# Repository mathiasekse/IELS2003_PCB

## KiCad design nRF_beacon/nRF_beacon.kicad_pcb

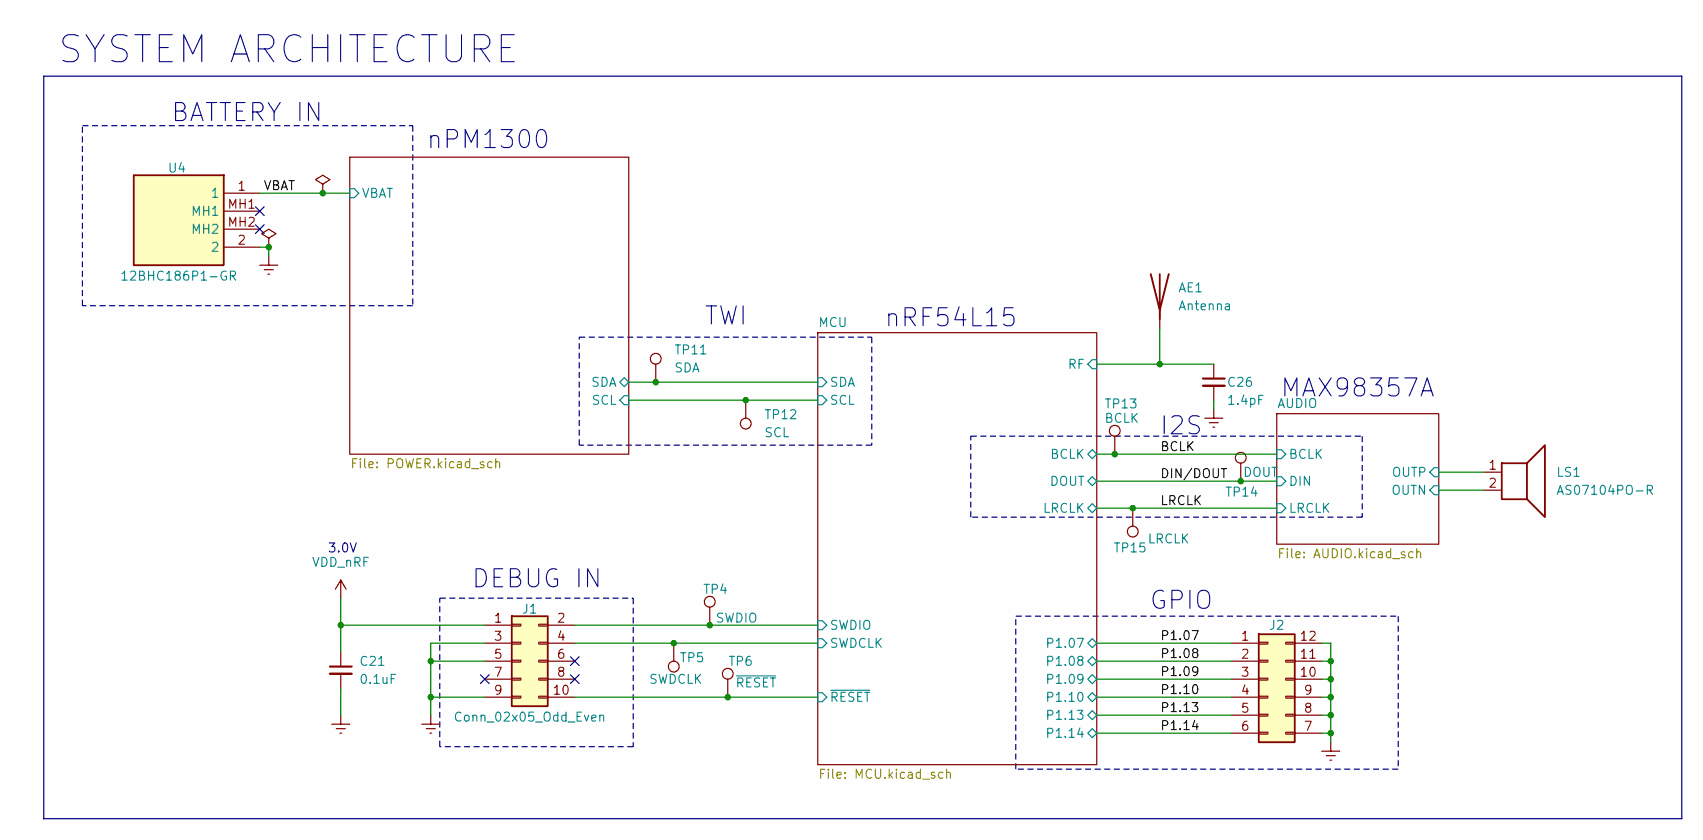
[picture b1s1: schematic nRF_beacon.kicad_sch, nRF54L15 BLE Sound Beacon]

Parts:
AE1: Antenna; PCB_Antenna
C21: 0.1uF; C_0201_0603Metric; MPN KGM03BR51E104KH
C26: 1.4pF; C_0201_0603Metric; MPN GCQ0335C1H1R4WB01D
J1: Conn_02x05_Odd_Even; FTSH-105-XX-YYY-DV-K-P-TR; MPN FTSH-105-01-F-DV-K-P
J2: Conn_02x03_Counter_Clockwise; PinHeader_2x06_P2.54mm_Vertical
LS1: AS07104PO-R; VN02A1500000G; MPN AS07104PO-R
TP4: SWDIO; TestPoint_Pad_D1.0mm
TP5: SWDCLK; TestPoint_Pad_D1.0mm
TP6: ~{RESET}; TestPoint_Pad_D1.0mm
TP11: SDA; TestPoint_Pad_D1.0mm
TP12: SCL; TestPoint_Pad_D1.0mm
TP13: BCLK; TestPoint_Pad_D1.0mm
TP14: DOUT; TestPoint_Pad_D1.0mm
TP15: LRCLK; TestPoint_Pad_D1.0mm
U4: 12BHC186P1-GR; 12BHC186P1GR; Manufacturer_Part_Number 12BHC186P1-GR; Mouser Part Number 12BHC186P1-GR

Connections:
/AUDIO/OUTN: LS1.2; also elsewhere on the board
/AUDIO/OUTP: LS1.1; also elsewhere on the board
/BCLK: TP13.1; also elsewhere on the board
/DIN/DOUT: TP14.1; also elsewhere on the board
/LRCLK: TP15.1; also elsewhere on the board
/MCU/RF: AE1.1 (A), C26.1; also elsewhere on the board
/MCU/SCL: TP12.1; also elsewhere on the board
/MCU/SDA: TP11.1; also elsewhere on the board
/MCU/SWDCLK: J1.4, TP5.1; also elsewhere on the board
/MCU/SWDIO: J1.2, TP4.1; also elsewhere on the board
/MCU/~RESET: J1.10, TP6.1; also elsewhere on the board
/P1.07: J2.1; also elsewhere on the board
/P1.08: J2.2; also elsewhere on the board
/P1.09: J2.3; also elsewhere on the board
/P1.10: J2.4; also elsewhere on the board
/P1.13: J2.5; also elsewhere on the board
/P1.14: J2.6; also elsewhere on the board
/VBAT: U4.1; also elsewhere on the board
GND: C21.2, C26.2, J1.3, J1.5, J1.9, J2.7, J2.8, J2.9, J2.10, J2.11, J2.12, U4.2; also elsewhere on the board
VDD_nRF: C21.1, J1.1; also elsewhere on the board

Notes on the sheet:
nPM1300
DEBUG IN
BATTERY IN
I2S
3.0V
GPIO
nRF54L15
TWI
SYSTEM ARCHITECTURE
MAX98357A

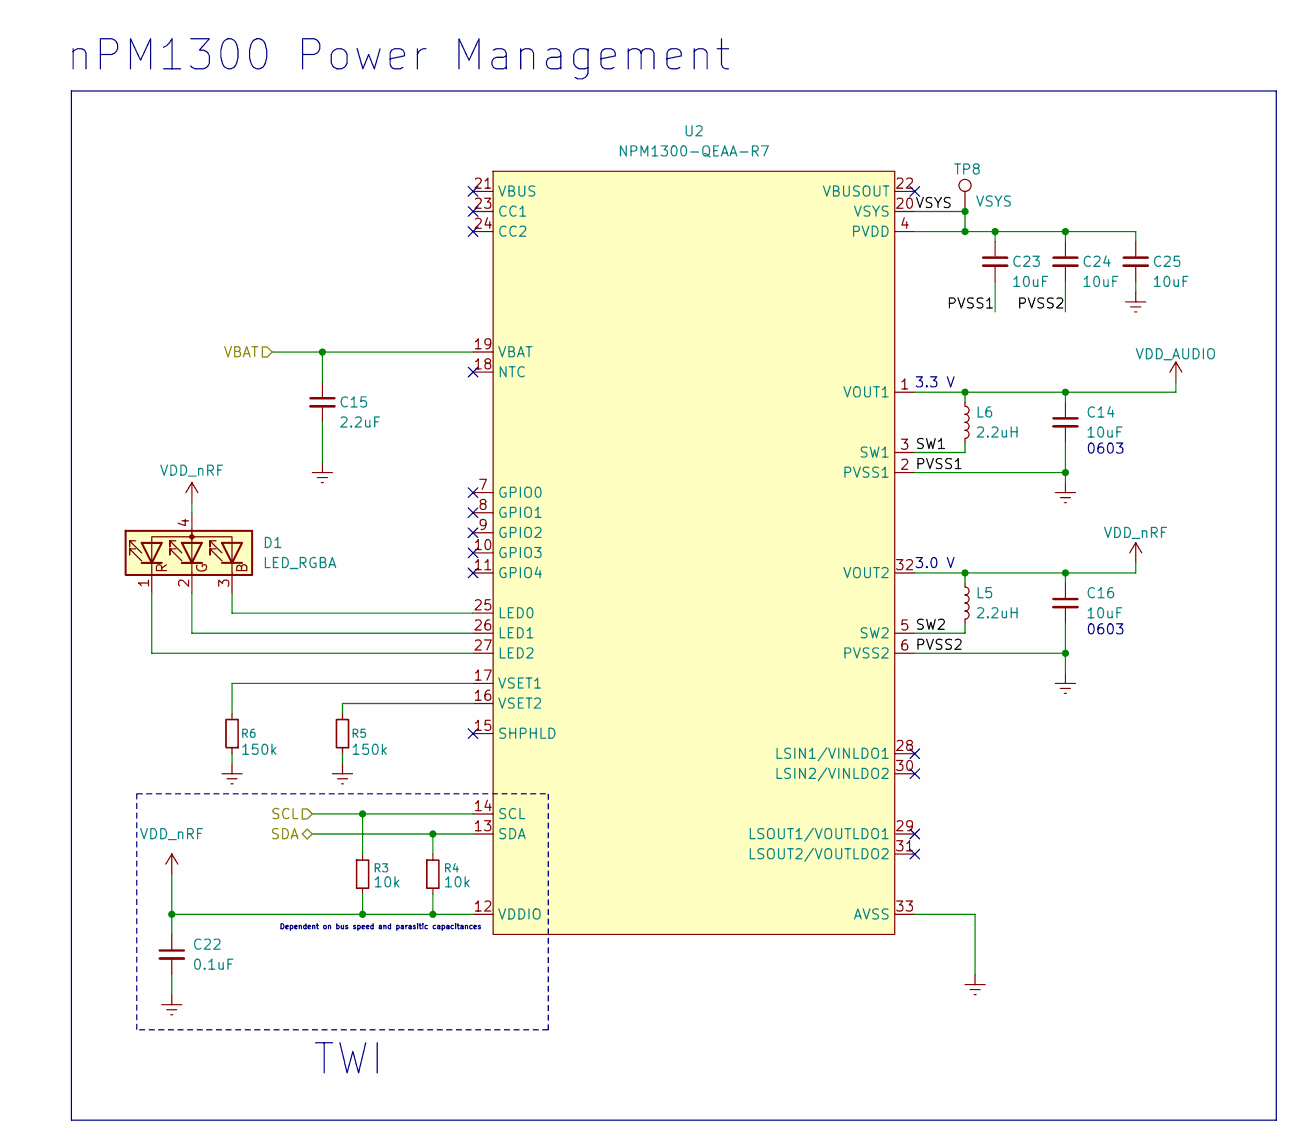
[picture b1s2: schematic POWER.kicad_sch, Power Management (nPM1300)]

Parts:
C14, C16, C23, C24, C25: 10uF; C_0603_1608Metric; MPN KGM15CR51E106KT
C15: 2.2uF; C_0603_1608Metric; MPN GRM188Z71C225KE43D
C22: 0.1uF; C_0201_0603Metric; MPN KGM03BR51E104KH
D1: LED_RGBA; APGF1012GBRC07; MPN APGF1012GBRC-07
L5, L6: 2.2uH; INDC2016X100N; MPN MLP2016V2R2MT0S1
R3, R4: 10k; R_0402_1005Metric; MPN CRCW040210K0FHEDP
R5, R6: 150k; R_0201_0603Metric; MPN CRCW0201150KFKED
TP8: VSYS; TestPoint_Pad_D1.0mm
U2: NPM1300-QEAA-R7; QFN-32_EP_5x5_Pitch0.5mm; MPN NPM1300-QEAA-R7

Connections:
/MCU/SCL: R3.1, U2.14 (SCL); also elsewhere on the board
/MCU/SDA: R4.1, U2.13 (SDA); also elsewhere on the board
/POWER/SW1: L6.2, U2.3 (SW1)
/POWER/SW2: L5.2, U2.5 (SW2)
/POWER/VSYS: C23.1, C24.1, C25.1, TP8.1, U2.4 (PVDD), U2.20 (VSYS)
/VBAT: C15.1, U2.19 (VBAT); also elsewhere on the board
GND: C14.2, C15.2, C16.2, C22.2, C23.2, C24.2, C25.2, R5.1, R6.1, U2.2 (PVSS1), U2.6 (PVSS2), U2.33 (AVSS); also elsewhere on the board
unnamed: D1.3 (BK), U2.25 (LED0)
unnamed: D1.2 (GK), U2.26 (LED1)
unnamed: D1.1 (RK), U2.27 (LED2)
unnamed: R6.2, U2.17 (VSET1)
unnamed: R5.2, U2.16 (VSET2)
VDD_AUDIO: C14.1, L6.1, U2.1 (VOUT1); also elsewhere on the board
VDD_nRF: C16.1, C22.1, D1.4 (A), L5.1, R3.2, R4.2, U2.12 (VDDIO), U2.32 (VOUT2); also elsewhere on the board

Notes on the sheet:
0603
TWI
3.3 V
nPM1300 Power Management
Dependent on bus speed and parasitic capacitances
3.0 V

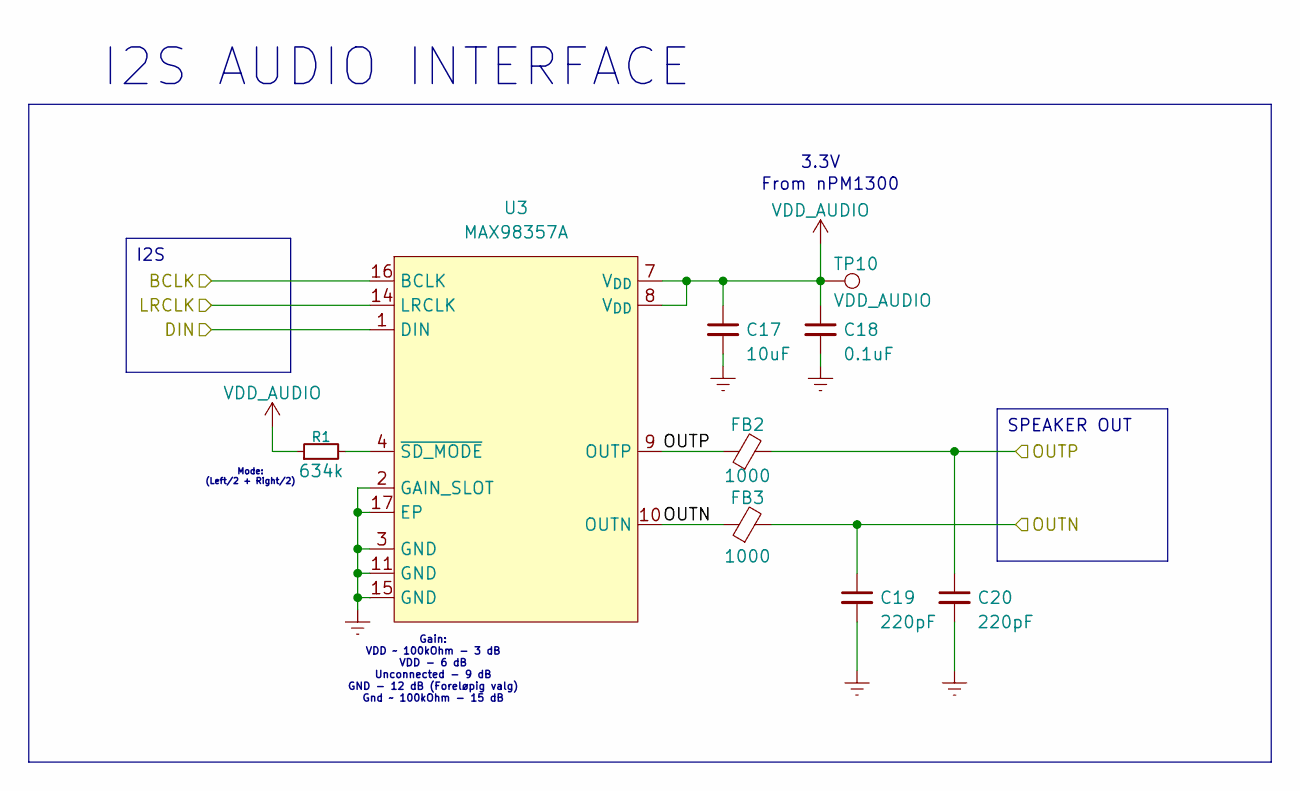
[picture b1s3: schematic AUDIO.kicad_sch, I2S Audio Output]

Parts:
C17: 10uF; C_0603_1608Metric; MPN KGM15CR51E106KT
C18: 0.1uF; C_0201_0603Metric; MPN KGM03BR51E104KH
C19, C20: 220pF; C_0603_1608Metric; MPN C0603C221J5RACTM
FB2, FB3: 1000; C_0805_2012Metric; MPN BLM21SP102SN1D
R1: 634k; R_0603_1608Metric; MPN CRCW0603634KDHTAP
TP10: VDD_AUDIO; TestPoint_Pad_D1.0mm
U3: MAX98357A; TQFN-16-1EP_3x3mm_P0.5mm_EP1.6x1.6mm; MPN MAX98357AETE+T

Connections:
/AUDIO/OUTN: C19.1, FB3.1, FB3.2, U3.10 (OUTN); also elsewhere on the board
/AUDIO/OUTP: C20.1, FB2.1, FB2.2, U3.9 (OUTP); also elsewhere on the board
/BCLK: U3.16 (BCLK); also elsewhere on the board
/DIN/DOUT: U3.1 (DIN); also elsewhere on the board
/LRCLK: U3.14 (LRCLK); also elsewhere on the board
GND: C17.2, C18.2, C19.2, C20.2, U3.2 (GAIN_SLOT), U3.3 (GND), U3.11 (GND), U3.15 (GND), U3.17 (EP); also elsewhere on the board
unnamed: R1.2, U3.4 (~SD_MODE)
VDD_AUDIO: C17.1, C18.1, R1.1, TP10.1, U3.7 (V_{DD}), U3.8 (V_{DD}); also elsewhere on the board

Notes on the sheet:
Gain: VDD ~ 100kOhm - 3 dB VDD - 6 dB Unconnected - 9 dB GND - 12 dB (Foreløpig valg) Gnd ~ 100kOhm - 15 dB
Mode: (Left/2 + Right/2)
From nPM1300
I2S AUDIO INTERFACE
3.3V
SPEAKER OUT
I2S

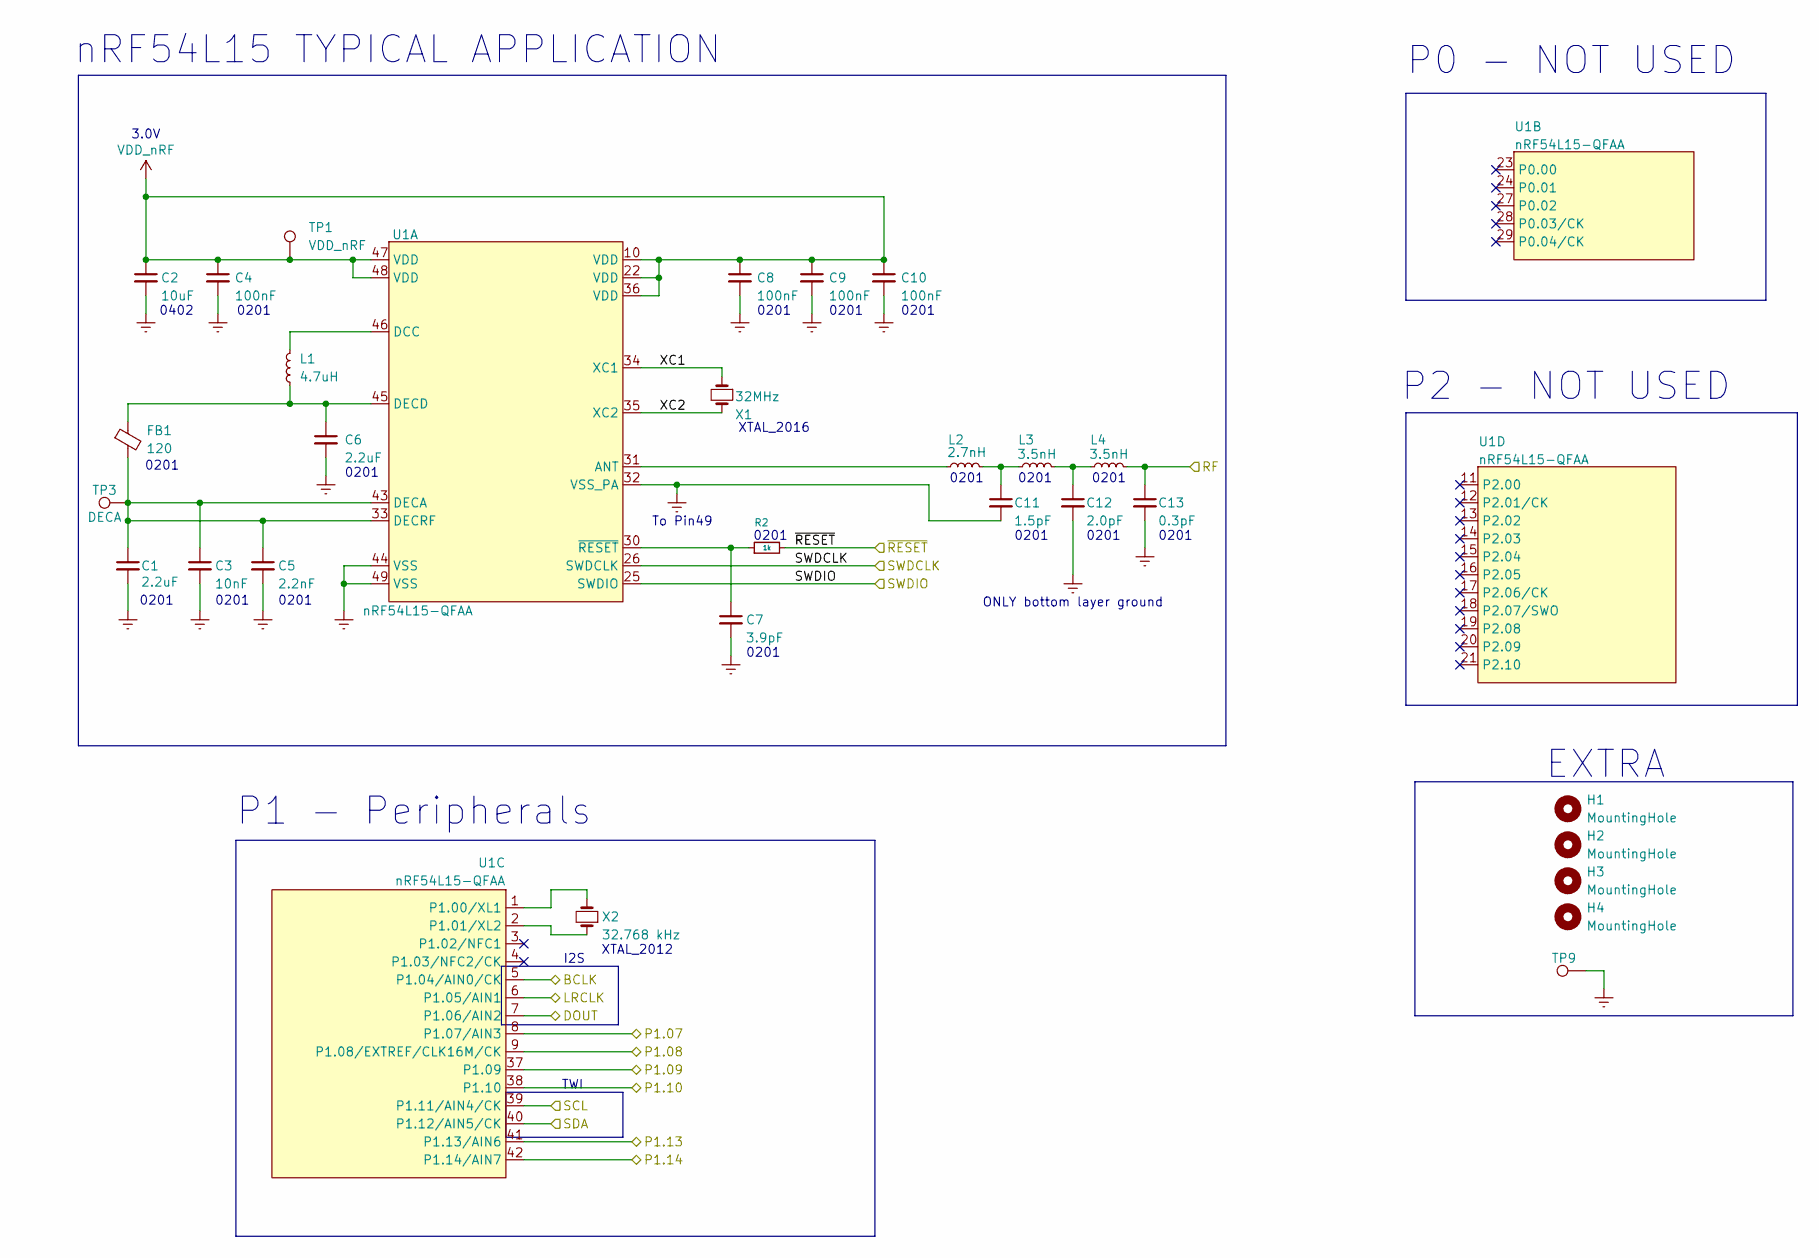
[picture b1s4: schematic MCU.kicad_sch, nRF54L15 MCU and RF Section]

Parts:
C1, C6: 2.2uF; C_0201_0603Metric; MPN GRM033D80E225ME47D
C2: 10uF; C_0402_1005Metric; MPN KGM05CS60J106MH
C3: 10nF; C_0201_0603Metric; MPN GRM033R70J103JA01D
C4, C8, C9, C10: 100nF; C_0201_0603Metric; MPN KGM03AR70J104KH
C5: 2.2nF; C_0201_0603Metric; MPN GRM033R71A222KA01D
C7: 3.9pF; C_0201_0603Metric; MPN GCQ0335C1H3R9CB01D
C11: 1.5pF; C_0201_0603Metric; MPN GJM0335C1E1R5WB01J
C12: 2.0pF; C_0201_0603Metric; MPN GJM0335C1E2R0WB01D
C13: 0.3pF; C_0201_0603Metric; MPN GCQ0335C1HR30BB01D
FB1: 120; L_0201_0603Metric; MPN MMZ0603Y121CT000
H1, H2: MountingHole; MountingHole_3.2mm_M3_Pad_Via
H3, H4: MountingHole; MountingHole_3.2mm_M3
L1: 4.7uH; L_0603_1608Metric; MPN LQM18PN4R7MFRL
L2: 2.7nH; L_0201_0603Metric; MPN LQP03HQ2N7B02D
L3, L4: 3.5nH; L_0201_0603Metric; MPN LQP03HQ3N5B02D
R2: 1k; R_0201_0603Metric; MPN RCA02011K00FNEDSR
TP1: VDD_nRF; TestPoint_Pad_D1.0mm
TP3: DECA; TestPoint_Pad_D1.0mm
TP9: GND; TestPoint_Pad_D1.0mm
U1: nRF54L15-QFAA; QFN-48_EP_6x6_Pitch0.4mm; MPN NRF54L15-QFAA-R7
X1: 32MHz; CX2016DB32000D0WZRC1; MPN CX2016DB32000D0WZRC1
X2: 32.768 kHz; Crystal_SMD_2012-2Pin_2.0x1.2mm; MPN CM8V-T1A-32.768kHz-9pF-20PPM-TB-QC

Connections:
/BCLK: U1.5 (P1.04/AIN0/CK); also elsewhere on the board
/DIN/DOUT: U1.7 (P1.06/AIN2); also elsewhere on the board
/LRCLK: U1.6 (P1.05/AIN1); also elsewhere on the board
/MCU/RF: C13.1, L4.2; also elsewhere on the board
/MCU/SCL: U1.39 (P1.11/AIN4/CK); also elsewhere on the board
/MCU/SDA: U1.40 (P1.12/AIN5/CK); also elsewhere on the board
/MCU/SWDCLK: U1.26 (SWDCLK); also elsewhere on the board
/MCU/SWDIO: U1.25 (SWDIO); also elsewhere on the board
/MCU/XC1: U1.34 (XC1), X1.1
/MCU/XC2: U1.35 (XC2), X1.3
/MCU/~RESET: R2.2; also elsewhere on the board
/P1.07: U1.8 (P1.07/AIN3); also elsewhere on the board
/P1.08: U1.9 (P1.08/EXTREF/CLK16M/CK); also elsewhere on the board
/P1.09: U1.37 (P1.09); also elsewhere on the board
/P1.10: U1.38 (P1.10); also elsewhere on the board
/P1.13: U1.41 (P1.13/AIN6); also elsewhere on the board
/P1.14: U1.42 (P1.14/AIN7); also elsewhere on the board
GND: C1.2, C2.2, C3.2, C4.2, C5.2, C6.2, C7.2, C8.2, C9.2, C10.2, C11.2, C12.2, C13.2, TP9.1, U1.32 (VSS_PA), U1.44 (VSS), U1.49 (VSS), X1.2, X1.4; also elsewhere on the board
unnamed: C11.1, L2.2, L3.1
unnamed: C12.1, L3.2, L4.1
unnamed: L2.1, U1.31 (ANT)
unnamed: L1.2, U1.46 (DCC)
unnamed: C1.1, C3.1, C5.1, FB1.2, TP3.1, U1.33 (DECRF), U1.43 (DECA)
unnamed: C6.1, FB1.1, L1.1, U1.45 (DECD)
unnamed: C7.1, R2.1, U1.30 (~RESET)
unnamed: U1.1 (P1.00/XL1), X2.2
unnamed: U1.2 (P1.01/XL2), X2.1
VDD_nRF: C2.1, C4.1, C8.1, C9.1, C10.1, TP1.1, U1.10 (VDD), U1.22 (VDD), U1.36 (VDD), U1.47 (VDD), U1.48 (VDD); also elsewhere on the board

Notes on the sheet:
0201
3.0V
XTAL_2012
P0 - NOT USED
0402
0201
XTAL_2016
nRF54L15 TYPICAL APPLICATION
P2 - NOT USED
TWI
P1 - Peripherals
ONLY bottom layer ground
EXTRA
To Pin49
I2S

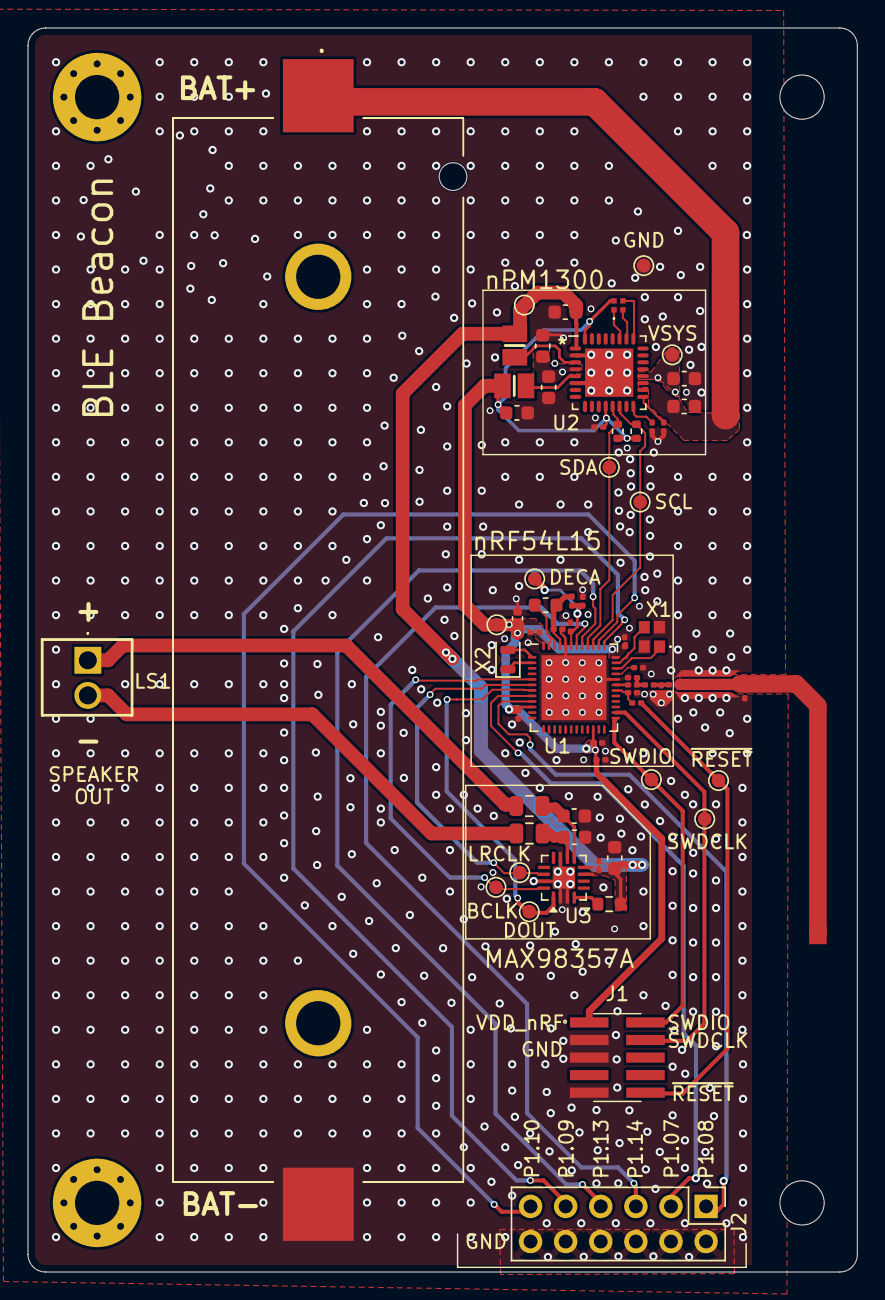
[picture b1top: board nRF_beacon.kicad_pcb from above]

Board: 4 copper layers, 60.0 x 90.0 mm, 69 parts (0 on the bottom side), 41 nets.

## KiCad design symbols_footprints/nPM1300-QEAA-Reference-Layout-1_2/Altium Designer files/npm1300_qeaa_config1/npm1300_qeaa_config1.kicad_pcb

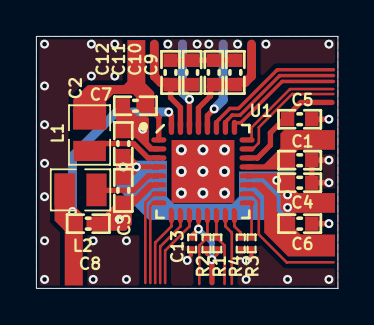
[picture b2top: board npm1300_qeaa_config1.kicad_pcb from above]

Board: 4 copper layers, 16.8 x 14.0 mm, 22 parts (0 on the bottom side), 18 nets.

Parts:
C1, C5: 1.0µF; CAPC1608X06L
C2, C3, C4, C7, C8, C9, C10, C11, C12: 10µF; CAPC1608X06L
C6: 2.2µF; CAPC1608X06L
C13: 100nF; CAPC0603X03L_C
L1, L2: 2.2µH; INDC2016X10N
NT1, NT2: Net tie; 2 PIN STARPOINT
R1, R2: 10k; RESC0603X03L_C
R3: 47k; RESC0603X03L_C
R4: 150k; RESC0603X03L_C
U1: nPM1300-QEAA; Nordic_QFN50P500X500X90-33N

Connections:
GND: C1.1, C4.1, C5.1, C6.1, C9.1, C10.1, C11.1, C12.1, C13.2, NT1.1, NT2.1, R3.2, R4.2, U1.33
PVSS1: C2.1, C7.1, NT1.2, U1.2
PVSS2: C3.1, C8.1, NT2.2, U1.6
SCL: R1.1, U1.14
SDA: R2.1, U1.13
SW1: L1.2, U1.3
SW2: L2.2, U1.5
VBAT: C6.2, U1.19
VBUSIN: C1.2, U1.21
VBUSOUT: C5.2, U1.22
VDDIO: C13.1, R1.2, R2.2, U1.12
VOUT1: C7.2, L1.1, U1.1
VOUT2: C8.2, L2.1, U1.32
VOUTLDO1: C9.2, C10.2, U1.29
VOUTLDO2: C11.2, C12.2, U1.31
VSET1: R3.1, U1.17
VSET2: R4.1, U1.16
VSYS: C2.2, C3.2, C4.2, U1.4, U1.20

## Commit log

2026-02-09 Lagt til .gitignore
2026-02-09 Opprettet prosjektfiler
2026-02-09 Lagt inn referanselayout for nRF54L15 (unntatt antenne matching network)
2026-02-10 Lagt til symbol og footprint filer til nRF54L15
2026-02-10 Added I2S audio interface schematic
2026-02-11 Added footprint and model for nRF and nPM
2026-02-11 Added reference layout files from Nordic for nPM1300 PMIC
2026-02-11 Created new symbol for nPM1300
2026-02-11 Added hierchical sheets for simple block diagram on root page, with complex circuits on their own page
2026-02-13 Finished typical application nRF. Added audio-block in root sheet.
2026-02-13 small optimizations in root schematics
2026-02-14 Added MPN and footprints for all components on nRF general application
2026-02-16 Added buck configuration for AUDIO 3.3V power. Removed USB input
2026-02-17 Updated nPM schematic. Added TWI and debug connector
2026-02-23 Added LEDs and BUCK supply from VSYS
2026-02-23 Finished first schematic draft. Ready for layout
2026-02-23 Roughly grouped components by function in PCB-layout
2026-02-26 Began matching network layout
2026-02-28 Added most of the components to nRF54 typical application layout
2026-02-28 Adjusted antenna layout
2026-03-01 Added transmission line, and new folder for report screenshots
2026-03-02 Began typical application around nPM1300
2026-03-03 Done a lot of work, connected all traces
2026-03-04 Cleaned up silkscreen
2026-03-04 Only 67 DRC errors left
2026-03-06 Continued fixing DRC errors. Increased trace width on several lines
2026-03-07 Adjustments to GPIO connector. Added testpads. Polygon pour by antenna for correct impedance matching
2026-03-07 Added stitching vias and completed DRC tests
2026-03-07 Added silkscreen braille, blind person logo and revision
2026-03-08 Completed layout for Revision A (Prototype). Created gerber files
